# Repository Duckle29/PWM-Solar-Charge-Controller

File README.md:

# PWM-Solar-Charge-Controller

I have decided to revive this project again. It's gonna be brought back as the PWM10, as It'll be designed to handle 10A, which is a little over a 140W panel.
The Rev2 files are designed using KiCAD

This is an attempt at making an Arduino powered PWM solar charge controller.

The design of this controller is heavily based on Julian Iletts PWM5 controller, which he sadly discontinued.
He however makes some interesting Youtube videos.

  * [Website](http://256.co.uk)
  * [Yoututbe](https://www.youtube.com/user/julius256)

This is **not** done, and there is no protection added to the board as of yet.
This first revision is simply as complete as I could make it, before my patience ran out for that day.
I might very well add the last few bits and bops within a few days.

### No Firmware has been written for this board as of yet
And as such, features and implementations of the hardware has yet to be decided.

### What is special about this spin-off of the PWM5?
This board is:
  * Entirely Arduino compatible, as it uses an ATMega328P
  * Able to measure the voltage of *both* the battery and panel, allowing for alternative control algorithms
  * Fitted with a slot for an NRF24L01+ Transceiver, for sending all available data back and forth / control the PWM charge controller. (After flashing the boot-loader, the solder bridges should be shorted for this feature)
  * Fitted with an RGB LED, that can be controlled to display all sorts of different color combinations and patterns
  * Designed to be cheaply mass produced, with purely SMT parts except for the headers for ISP, NRF and FTDI.

### What needs to be done?
The following things need to be added:
  * Reverse polarity protection
  * Short circuit protection
  * A thorough check of the schematic and board. I slapped this together in one 8 hour sitting, so I'm bound to have missed something / messed something up
  * Firmware needs to be written
  * It needs to be tested in general.
  * Parts need to be checked for availability and pricing. If none are available in the used footprint, a substitute has to be found.

### Additional notes
If I decide the board is ready to go, I will order some assembled boards. If people are interested in some assembled boards, then comment in the issue that I opened for that purpose. I might order some home and send them to you for the price it cost me, and nothing more (that's assembled board cost + shipping)

### Renders:

Greetings!

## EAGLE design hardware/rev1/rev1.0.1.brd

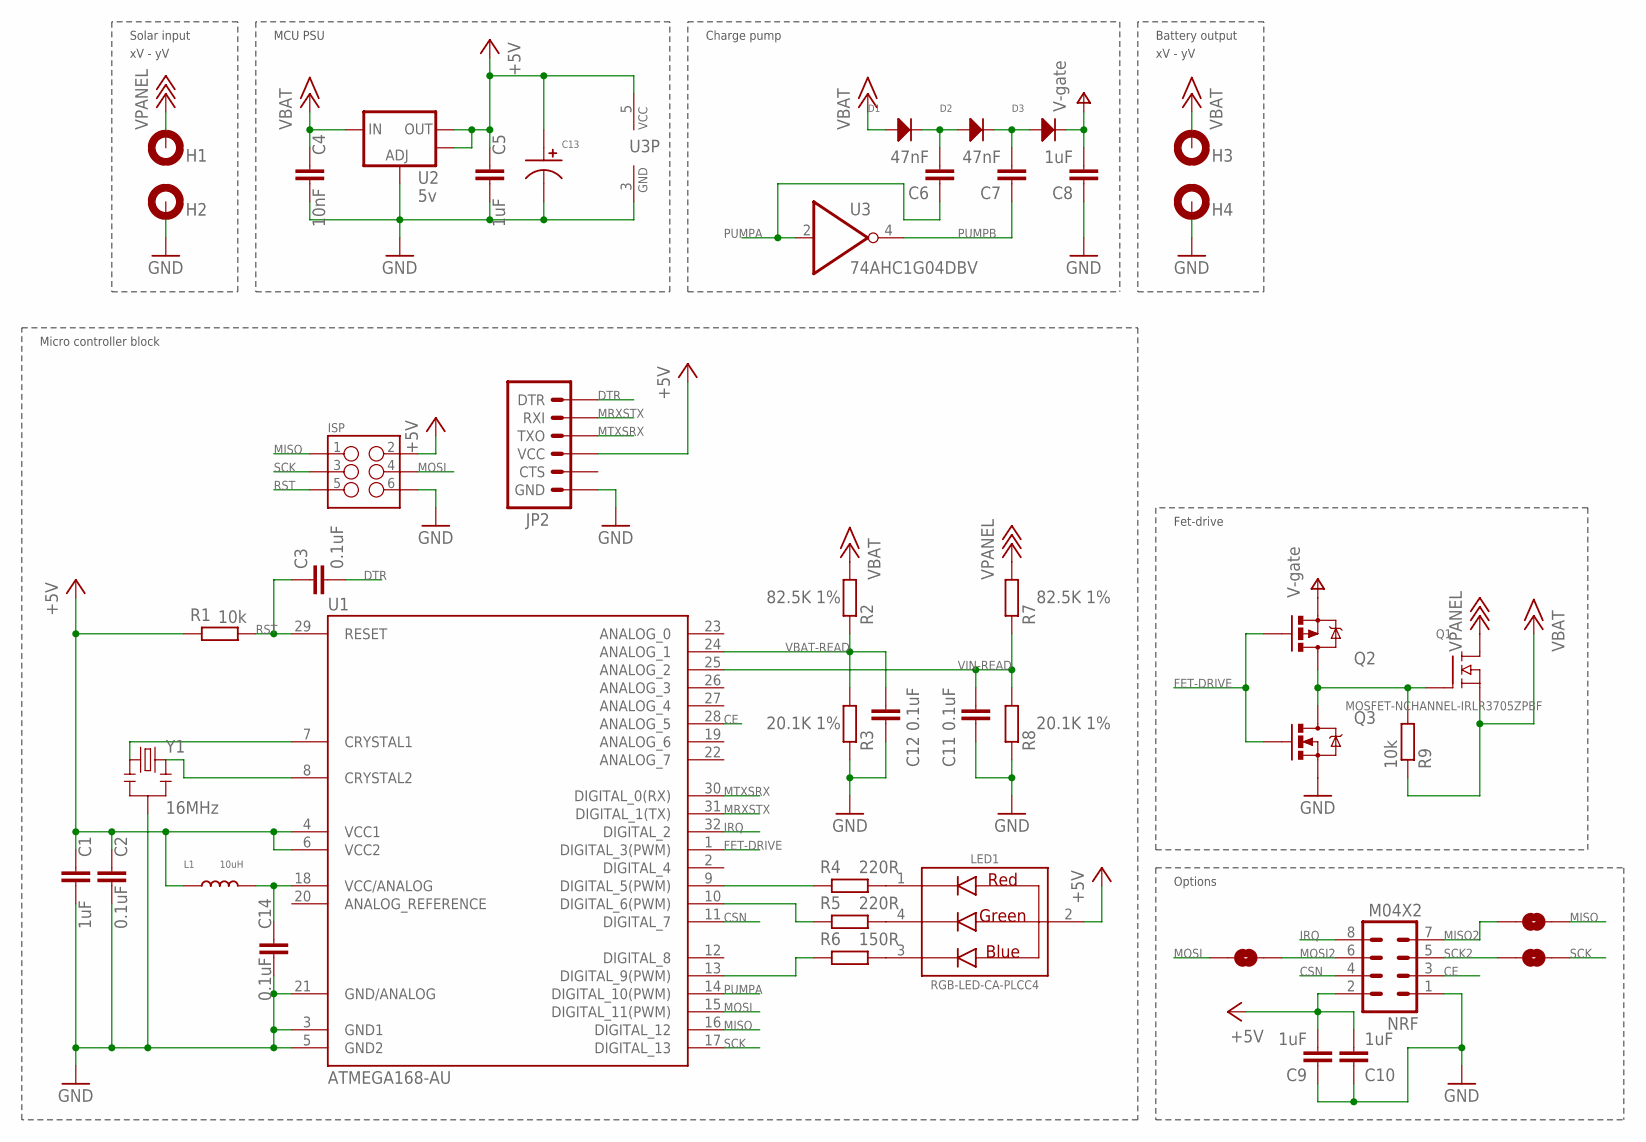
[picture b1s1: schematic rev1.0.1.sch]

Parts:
C1, C5, C8, C9, C10: 1uF; C0603K
C2, C3, C11, C12, C14: 0.1uF; C0603K
C4: 10nF; C0603K
C6, C7: 47nF; C0603K
C13: CAPACITOR_P_4MM; CP4MM
D1, D2, D3: DIODE_SOD-123; SOD-123
H1, H2, H3, H4: MOUNT-PAD-ROUND3.0; 3,0-PAD
ISP: M03X22X3_SILK_SM; 2X3
JP2: ARDUINO_SERIAL_PROGRAMLOCK; 1X06_LOCK
L1: 10uH; L1210
LED1: RGB-LED-CA-PLCC4; PLCC4
NRF: M04X2; 2X4
Q1: MOSFET-NCHANNEL-IRLR3705ZPBF; DPAK
Q2: MOSFET-PCHANNEL; SOT23
Q3: MOSFET-NCHANNELBSS138; SOT23
R1, R9: 10k; R0603
R2, R7: 82.5K 1%; R0603
R3, R8: 20.1K 1%; R0603
R4, R5: 220R; R0603
R6: 150R; R0603
SJ2, SJ5, SJ6: SOLDERJUMPERNO; SJ_2S-NO
U1: ATMEGA168-AU; TQFP32-08
U2: 5v; SOT223
U3: 74AHC1G04DBV; SOT23-5
Y1: 16MHz; RESONATOR-SMD

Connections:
+5V: C1.1, C2.1, C5.1, C9.2, C10.2, C13.P$1, ISP.2, JP2.4 (VCC), L1.P$1, LED1.2 (CA), NRF.2, R1.2, U1.4 (VCC1), U1.6 (VCC2), U2.2 (OUT), U2.4 (OUT), U3.5 (VCC)
+15V: C4.1, D1.ANODE, H3.B3,0, Q1.2 (S), R2.2, R9.1, U2.3 (IN)
+18V: H1.B3,0, Q1.TAB (D), R7.2
CE: NRF.3, U1.28 (ANALOG_5)
CSN: NRF.4, U1.11 (DIGITAL_7)
DTR: C3.2, JP2.1 (DTR)
FET-DRIVE: Q2.1 (G), Q3.1 (G), U1.1 (DIGITAL_3(PWM))
FET-PUMP: Q1.1 (G), Q2.3 (D), Q3.3 (D), R9.2
GND: C1.2, C2.2, C4.2, C5.2, C8.1, C9.1, C10.1, C11.1, C12.1, C13.P$2, C14.2, H2.B3,0, H4.B3,0, ISP.6, JP2.6 (GND), NRF.1, Q3.2 (S), R3.1, R8.1, U1.3 (GND1), U1.5 (GND2), U1.21 (GND/ANALOG), U2.1 (ADJ), U3.3 (GND), Y1.2
IRQ: NRF.8, U1.32 (DIGITAL_2)
MISO: ISP.1, SJ6.2, U1.16 (DIGITAL_12)
MISO2: NRF.7, SJ6.1
MOSI: ISP.4, SJ2.1, U1.15 (DIGITAL_11(PWM))
MOSI2: NRF.6, SJ2.2
MRXSTX: JP2.2 (RXI), U1.31 (DIGITAL_1(TX))
MTXSRX: JP2.3 (TXO), U1.30 (DIGITAL_0(RX))
unnamed: U1.8 (CRYSTAL2), Y1.3
unnamed: U1.7 (CRYSTAL1), Y1.1
unnamed: R4.2, U1.9 (DIGITAL_5(PWM))
unnamed: LED1.4 (GC), R5.1
unnamed: LED1.1 (RC), R4.1
unnamed: LED1.3 (BC), R6.1
unnamed: R5.2, U1.10 (DIGITAL_6(PWM))
unnamed: C7.2, D2.CATHODE, D3.ANODE
unnamed: R6.2, U1.13 (DIGITAL_9(PWM))
unnamed: C6.2, D1.CATHODE, D2.ANODE
unnamed: C14.1, L1.P$2, U1.18 (VCC/ANALOG)
PUMPA: C6.1, U1.14 (DIGITAL_10(PWM)), U3.2 (I)
PUMPB: C7.1, U3.4 (O)
RST: C3.1, ISP.5, R1.1, U1.29 (RESET)
SCK: ISP.3, SJ5.2, U1.17 (DIGITAL_13)
SCK2: NRF.5, SJ5.1
V+: C8.2, D3.CATHODE, Q2.2 (S)
VBAT-READ: C12.2, R2.1, R3.2, U1.24 (ANALOG_1)
VIN-READ: C11.2, R7.1, R8.2, U1.25 (ANALOG_2)

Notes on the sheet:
Solar input
xV - yV
Micro controller block
Options
MCU PSU
Battery output
Fet-drive
Charge pump

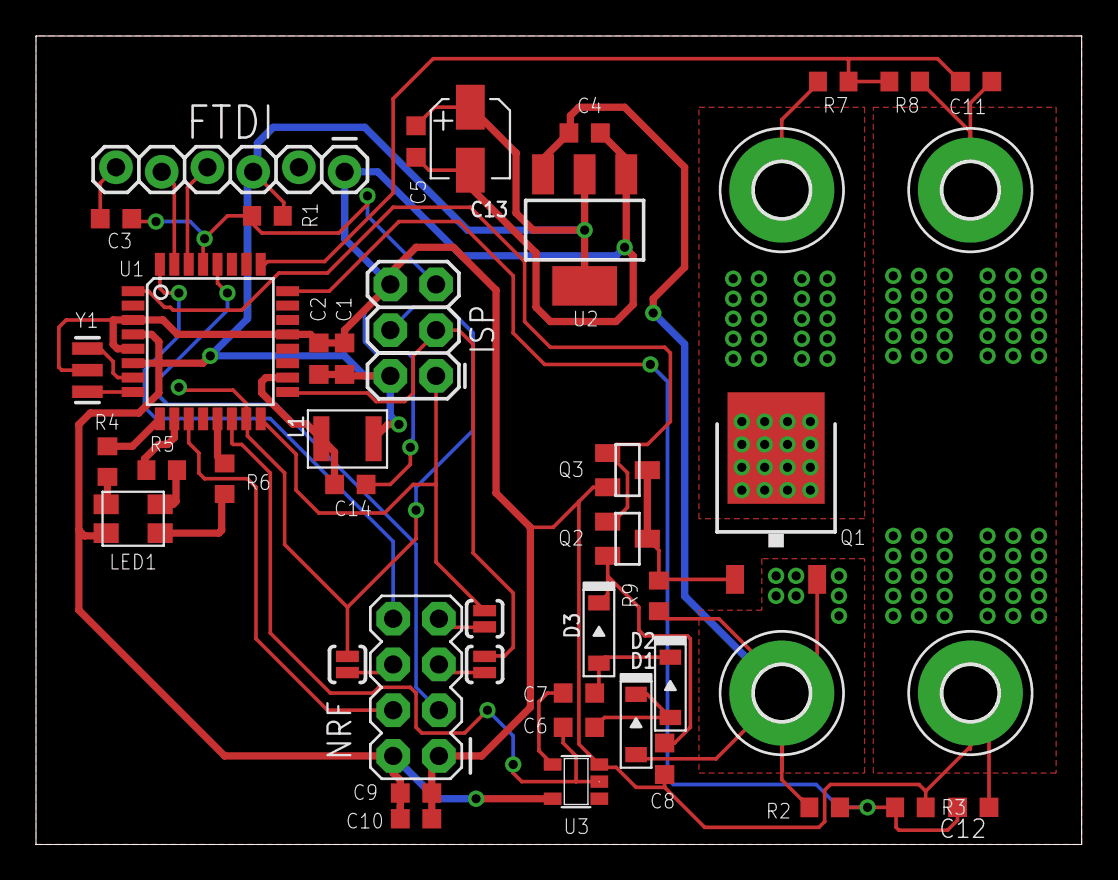
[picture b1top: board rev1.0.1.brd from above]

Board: 2 copper layers, 58.1 x 44.9 mm, 45 parts (0 on the bottom side), 35 nets.

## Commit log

2015-04-15 Added charge pump for v-gate
2015-04-15 Schematic pre-finished. Needs values added
2015-04-15 Board laid out
2015-04-15 Fixing LDO input pin
2015-04-15 Added copper pour, sorted silk screen
2015-04-15 Added PDF of both schematic and board
2015-04-15 Added dimentions to the board
2015-04-15 Wrote the readme
2015-04-15 Correct Julians last name. Sorry
2015-04-15 Added MIT License
2015-04-15 Corrected some erros in the readme
2015-04-15 Made a hardware and firmware folder
2015-04-15 Propperly filtered AVCC
2015-04-15 Fixed copper ground pour
2015-04-15 Updated PDF files to reflect latest commits
2017-05-23 Finished schematic of Rev2
2017-05-23 doing some stupid shit to rename rev1
2017-05-23 Renamed rev1 to Rev1
2017-05-29 created PCB and gerbers
2017-05-29 Added renders
2017-05-29 Added renders to readme. Let's see how huge they are

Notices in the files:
parts and their libraries:
SparkFun-Connectors: Licensing: CC v3.0 Share-Alike You are welcome to use this library for commercial purposes.
